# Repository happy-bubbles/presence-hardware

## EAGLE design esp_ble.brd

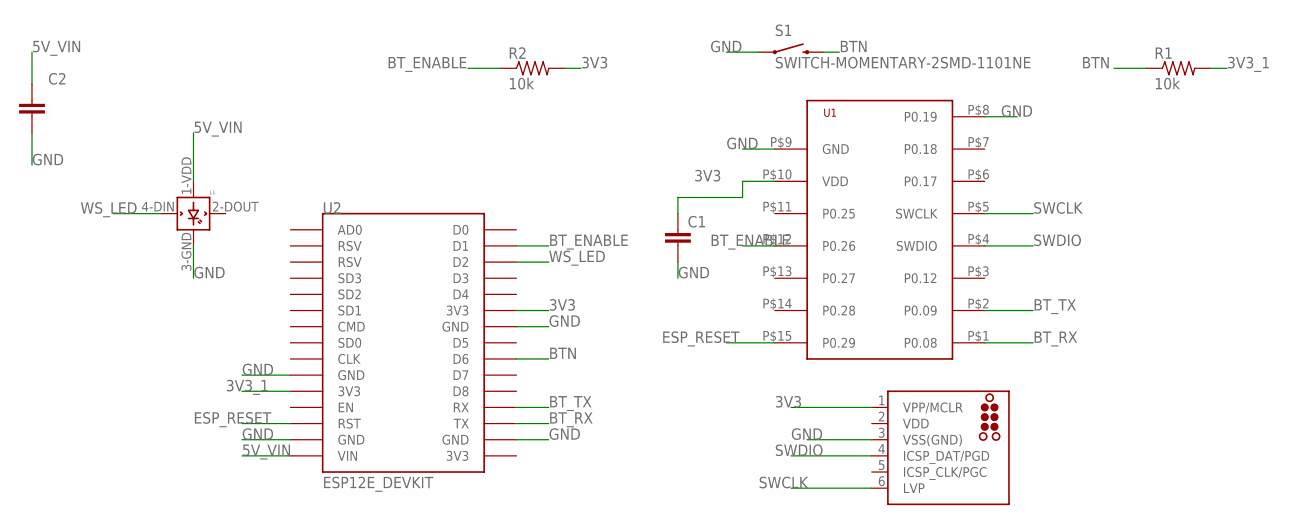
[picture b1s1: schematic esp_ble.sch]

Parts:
C1: CAP0603-CAP; 0603-CAP
C2: CAPACITOR_NPOL-0603; C603
J1: TC2030-MCP-NL
L1: WS2812B
R1, R2: 10k; R0603
S1: SWITCH-MOMENTARY-2SMD-1101NE; TACTILE-SWITCH-1101NE
U1: PTR5518
U2: ESP12E_DEVKIT

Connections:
3V3: C1.1, J1.1 (VPP/MCLR), R2.2, U1.P$10 (VDD), U2.3V3@1 (3V3)
3V3_1: R1.2, U2.3V3@0 (3V3)
5V_VIN: C2.1, L1.1-VDD (VDD), U2.VIN
BTN: R1.1, S1.2, U2.D6
BT_ENABLE: R2.1, U1.P$12 (P0.26), U2.D1
BT_RX: U1.P$1 (P0.08), U2.TX
BT_TX: U1.P$2 (P0.09), U2.RX
ESP_RESET: U1.P$15 (P0.29), U2.RST
GND: C1.2, C2.2, J1.3 (VSS(GND)), L1.3-GND (GND), S1.1, U1.P$8 (P0.19), U1.P$9 (GND), U2.GND@0 (GND), U2.GND@1 (GND), U2.GND@2 (GND), U2.GND@3 (GND)
SWCLK: J1.6 (LVP), U1.P$5 (SWCLK)
SWDIO: J1.4 (ICSP_DAT/PGD), U1.P$4 (SWDIO)
VDD: J1.2 (VDD)
WS_LED: L1.4-DIN (DIN), U2.D2

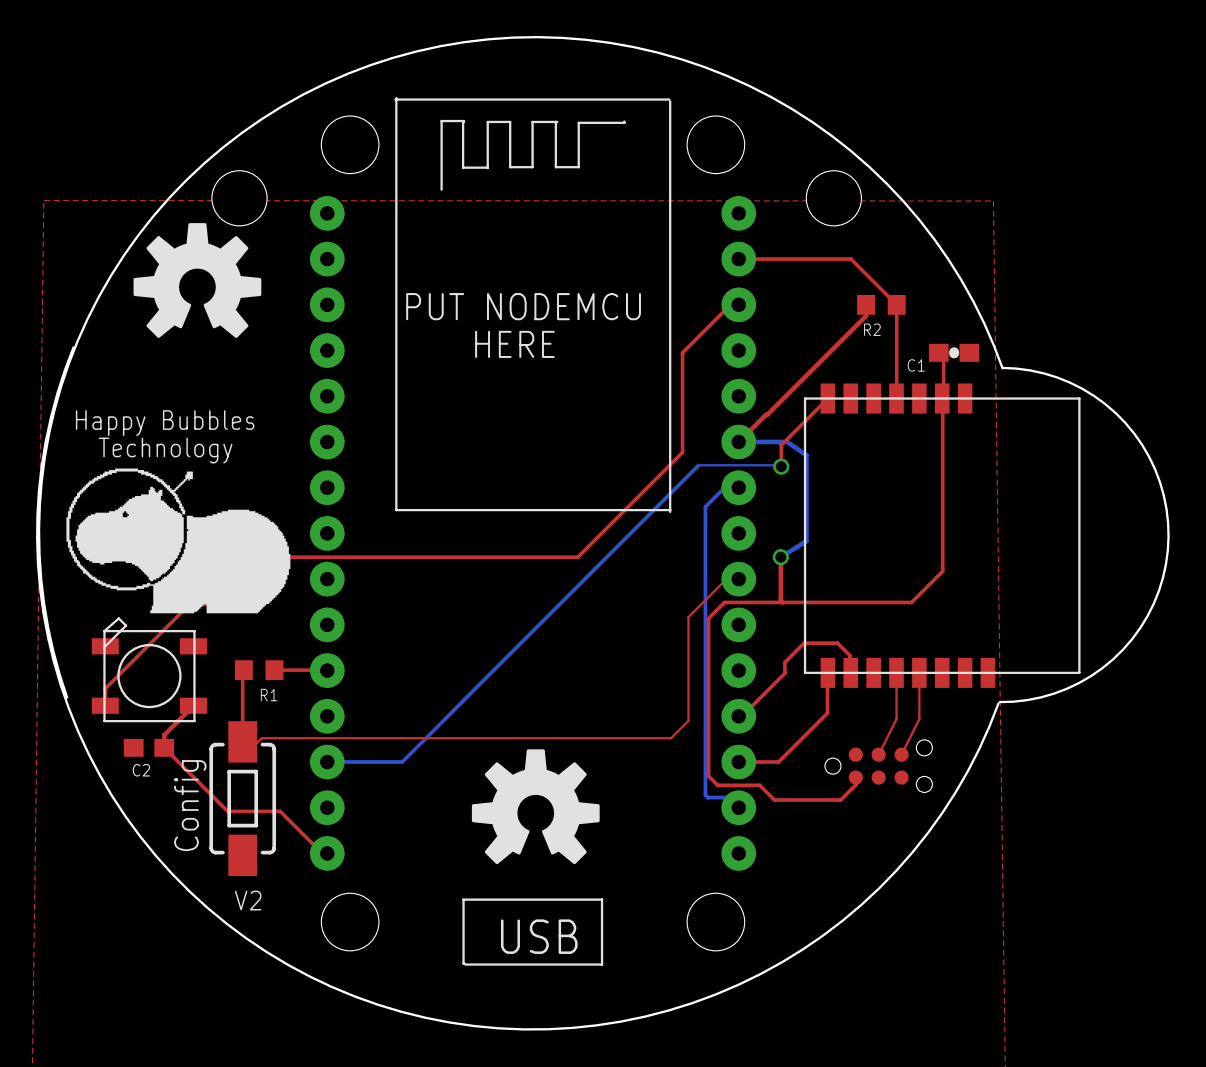
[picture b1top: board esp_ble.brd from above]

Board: 2 copper layers, 62.9 x 55.1 mm, 13 parts (1 on the bottom side), 12 nets.

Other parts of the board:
U$1: HAPPY_HIPPO_500MIL
U$4, U$6: OSHW-LOGO-L
U$5: HAPPY_HIPPO

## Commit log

2016-07-13 fix slash error
    change slash to comma. github will present it in better way

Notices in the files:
parts and their libraries:
SparkFun: Licensing: CC v3.0 Share-Alike You are welcome to use this library for commercial purposes.
tag-connect: ©2009 ROFA.cz - modified and updated by Robert Darlington ‹rdarlington@gmail.com›
